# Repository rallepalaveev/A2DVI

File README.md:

# A2DVI - Apple II Digital Video

This is a project for a digital DVI/HDMI Apple II video card.
It directly produces a digital video stream from Apple II's memory content.
The signal is output via an HDMI connector, connecting the Apple II to modern displays with HDMI (or DVI) inputs.
No more analog signal conversion required.

The project is a collaboration with Thorsten Brehm. His related firmware project is here: https://github.com/ThorstenBr/A2DVI-Firmware

For the DVI output to be active, the new firmware developed by Thorsten should be used.

The card also has an alternative analog VGA connector.
For the VGA output to be active, the [VGA firmware](https://github.com/markadev/AppleII-VGA) developed by Mark Aikens should be used.

The card can produce either an analog VGA or a digital HDMI signal, but not both simultaneously.
To switch between modes, a firmware update is required and opening/closing connections.

As of v2.0 VGA function is not supported - the card is DVI only.

V2.2 has an onboard driver to invoke the configuation utility by PR#N, where N is the slot number.

V2.3 is a TH version with 74HC245 and requires a DVI break-out board.

V2.4 is a TH version with 74HC244 and requires a DVI break-out board.

## Procedure to activate DVI mode
* v1.2:
  program [A2DVI-Firmware](https://github.com/ThorstenBr/A2DVI-Firmware) to RPI Pico;
  remove U6 and disconnect pins 11, 12 and 13 of U5.
* v1.5:
  program [A2DVI-Firmware](https://github.com/ThorstenBr/A2DVI-Firmware) to RPI Pico;
  open all 9 DIP switches.
* v1.6:
  program [A2DVI-Firmware](https://github.com/ThorstenBr/A2DVI-Firmware) to RPI Pico;
  desloder the 8 soldering pads at GPIOs 14-21.
* v1.7:
  program [A2DVI-Firmware](https://github.com/ThorstenBr/A2DVI-Firmware) to RPI Pico;
  desloder the 8 soldering pads at GPIOs 14-21; remove VGA sub-board and ribbon cable.
* v2.0:
  program [A2DVI-Firmware](https://github.com/ThorstenBr/A2DVI-Firmware) to RPI Pico.
* v2.2:
  program [A2DVI-Firmware](https://github.com/ThorstenBr/A2DVI-Firmware) to RPI Pico.
* v2.3:
  program [A2DVI-Firmware](https://github.com/ThorstenBr/A2DVI-Firmware) to RPI Pico.
* v2.4:
  program [A2DVI-Firmware](https://github.com/ThorstenBr/A2DVI-Firmware) to RPI Pico.
  
## Procedure to activate VGA mode
* v1.2:
  program [VGA firmware](https://github.com/markadev/AppleII-VGA) to RPI Pico;
  replace U5 and U6.
* v1.5:
  program [VGA firmware](https://github.com/markadev/AppleII-VGA) to RPI Pico;
  close all 9 DIP switches.
* v1.6:
  program [VGA firmware](https://github.com/markadev/AppleII-VGA) to RPI Pico;
  sloder the 8 soldering pads at GPIOs 14-21.
* v1.7:
  program [VGA firmware](https://github.com/markadev/AppleII-VGA) to RPI Pico;
  sloder the 8 soldering pads at GPIOs 14-21; connect VGA sub-board to main board by the ribbon cable.
* v2.0:
  N.A. - v2.0 is HDMI only.
* v2.2:
  N.A. - v2.2 is HDMI only.
* v2.3:
  N.A. - v2.3 is HDMI only.
* v2.4:
  N.A. - v2.4 is HDMI only.
* v4.4:
  N.A. - v4.4 is HDMI only.
* v4.6:
  N.A. - v4.6 is HDMI only.
  * v5.x:
  N.A. - v5.x are HDMI only.

Note: In version 2.4 I experimented with replacing the 8x 270-ohms resistors on the DVI lines by 100pF capacitors to achieve better separation form potential 3.3V DC leak from the screen; while this worked, some screens are more prone to noise and results may still be better with the 270-ohms resistors.

Note2: Version 4.4 is bidirectional and can work as a variety of functionalities. Firmware is closed source so far. V4.6 has some optimizations.

Note3: Versions 5.x are based on CPB with RP2354B and are 5V tolerant and has 48 GPIOs available. This eliminates the need
for level shifting and multiplexing. This version had DVI function and can support RTC via a dedicated connector.

## Dual-Language Support
The pin on the v1.5 and later boards is for AltChr connection, supported by A2DVI firmware for switching between alternative character sets on non-US versions of Apple II ("Euro-machines").

# Hardware
* Based on the PICO controller board.
* Provides a DVI video stream via an HDMI connector.
* Low power/heat dissipation: less than 70mA@5V = 0.35W in operation.
* Uses 4x 74LV245 bus transceivers for 5V/3.3V signal conversion of the Apple II bus.
* Separate ALTCHR input pin for dual-language support: pin needs to be wired separately to the "language switch" of Euro-Apple IIs (optional).
* Versions 5.x do not need level shifters.

# Thanks
This is a project based on:

* the AppleII-VGA project by Mark Aikens - https://github.com/markadev/AppleII-VGA

* the PicoDVI project by Luke Wren - https://github.com/Wren6991/PicoDVI

* Thorsten Brehm for firmware development and board design considerations

* Oliver Schmidt on original idea discussions and design considerations

* Mike Neil for adapting the firmware for v5.x.

# License
Board design by Ralle Palaveev (c) 2026.

All rights reserved.

Redistribution and use in source, binary, and manufactured forms, with or without
modification, are permitted provided that the following conditions are met:
1. Redistributions of source code and design files must retain the above copyright
   notice, this list of conditions and the following disclaimer.
2. Redistributions in binary or manufactured form must reproduce the above copyright
   notice, this list of conditions and the following disclaimer in the
   documentation and/or other materials provided with the distribution.
3. All advertising materials mentioning features or use of this software
   or hardware must display the following acknowledgement:
   This product includes software or hardware developed by Ralle Palaveev.
4. Neither the name of Ralle Palaveev nor the
   names of its contributors may be used to endorse or promote products
   derived from this software or hardware without specific prior written permission.

The above copyright notice and this permission notice shall be included in all
copies or substantial portions of the Software.

THE SOFTWARE IS PROVIDED "AS IS", WITHOUT WARRANTY OF ANY KIND, EXPRESS OR
IMPLIED, INCLUDING BUT NOT LIMITED TO THE WARRANTIES OF MERCHANTABILITY,
FITNESS FOR A PARTICULAR PURPOSE AND NONINFRINGEMENT. IN NO EVENT SHALL THE
AUTHORS OR COPYRIGHT HOLDERS BE LIABLE FOR ANY CLAIM, DAMAGES OR OTHER
LIABILITY, WHETHER IN AN ACTION OF CONTRACT, TORT OR OTHERWISE, ARISING FROM,
OUT OF OR IN CONNECTION WITH THE SOFTWARE OR THE USE OR OTHER DEALINGS IN THE
SOFTWARE.

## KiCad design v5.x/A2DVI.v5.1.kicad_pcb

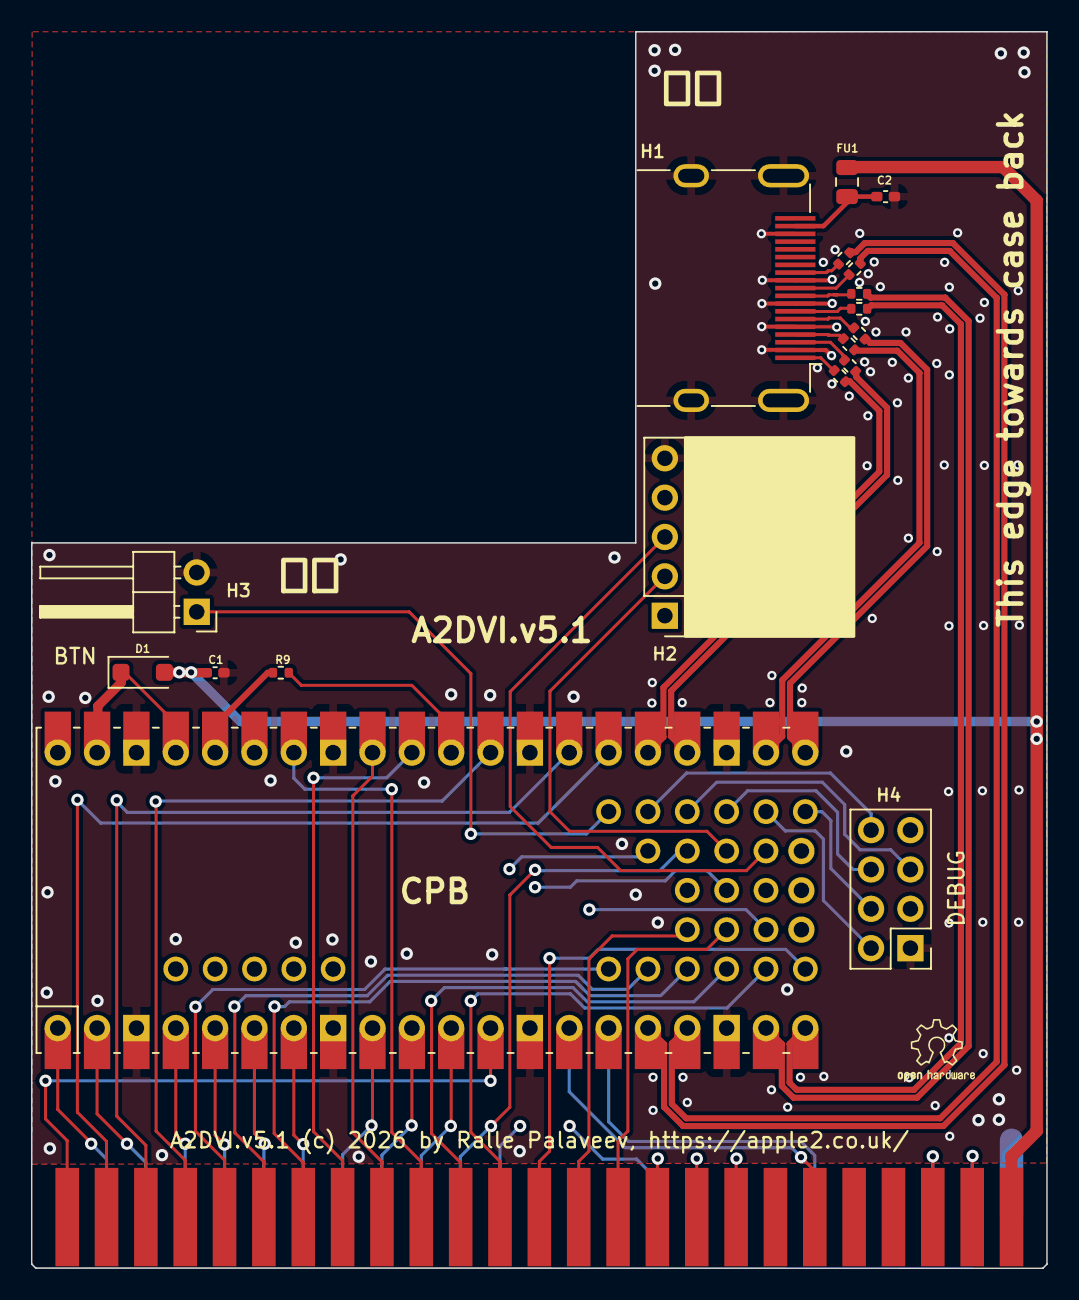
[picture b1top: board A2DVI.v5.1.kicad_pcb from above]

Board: 4 copper layers, 65.5 x 79.8 mm, 18 parts (0 on the bottom side), 22 nets.

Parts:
C1, C2: 100n; C_0402_1005Metric_Pad0.74x0.62mm_HandSolder
D1: D_SOD-123F
FU1: 100mA; Fuse_0805_2012Metric
H1: HDMI_A_Molex_208658-1001_Horizontal
H2: PinHeader_1x05_P2.54mm_Vertical
H3: PinHeader_1x02_P2.54mm_Horizontal
H4: PinHeader_2x04_P2.54mm_Vertical
R1, R2, R3, R4, R5, R6, R7, R8: 270; R_0402_1005Metric
R9: 1k; R_0402_1005Metric
U1: CPB; CPB_SMD_TH

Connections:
3.3V: H2.1, H4.7, R9.2, U1.36
5V: C1.2, D1.2, FU1.2
5V_out: C2.2, FU1.1, H1.18
BTN: H3.1, U1.41
CLK_N: R8.1, U1.16
CLK_P: R7.1, U1.17
CS: H4.4, U1.46
D0_N: R6.1, U1.19
D0_P: R5.1, U1.20
D1_N: R4.1, U1.21
D1_P: R3.1, U1.22
D2_N: R2.1, U1.24
D2_P: R1.1, U1.25
GND: C1.1, C2.1, H1.2, H1.5, H1.8, H1.11, H1.17, H1.SH, H2.5, H3.2, H4.1, U1.3, U1.8, U1.13, U1.18, U1.23, U1.28, U1.33, U1.38
I2C_SCL: H2.3, U1.50
I2C_SDA: H2.2, U1.49
LED: H4.8, U1.42
RUN: R9.1, U1.30
UART_RX: H4.6, U1.44
UART_TX: H4.5, U1.43
UART_extra: H4.2, U1.45
VSYS: D1.1, U1.37, U1.39

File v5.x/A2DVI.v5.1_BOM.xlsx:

Comment | Designator | Footprint | JLCPCB Part #（optional）
16V 100nF X7R ±10% 0402 Multilayer Ceramic Capacitors MLCC - SMD/SMT ROHS | C1,C2 | 0402 | C1525
DSS14 | D1 | SOD-123FL | C2923923
6V 500mA Resettable Fuse | FU1 | 0805-50 | C269104
HDMI connector | H1 |  | C2906135
270 | R1,R2,R3,R4,R5,R6,R7,R8 | 0402 | C324790
1k | R9 | 0402 | C11702

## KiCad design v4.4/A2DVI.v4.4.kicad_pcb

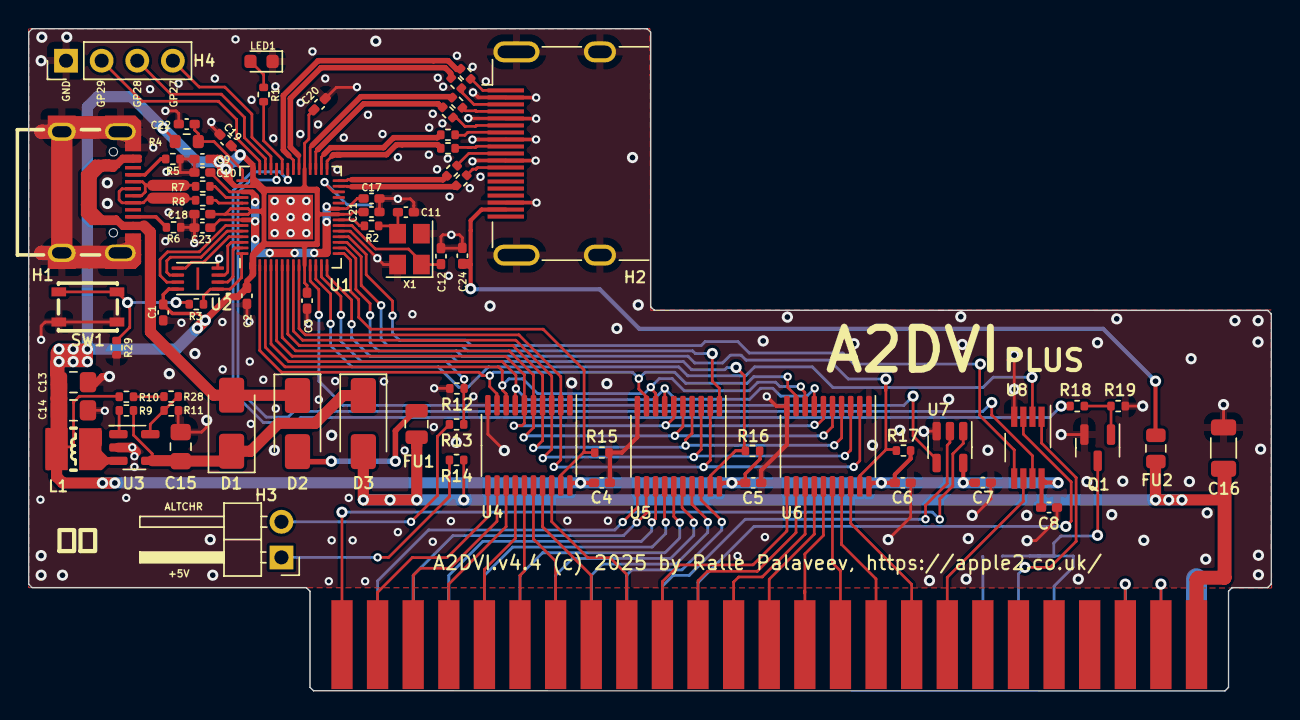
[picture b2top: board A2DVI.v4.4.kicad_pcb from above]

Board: 2 copper layers, 88.6 x 47.2 mm, 75 parts (0 on the bottom side), 63 nets.

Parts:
C1, C2, C3, C4, C5, C6, C7, C8, C17, C18, C19, C20, C21, C22, C23, C24: 100n; C_0402_1005Metric_Pad0.74x0.62mm_HandSolder
C9, C10: 2u2; C_0402_1005Metric_Pad0.74x0.62mm_HandSolder
C11, C12: 15p; C_0402_1005Metric_Pad0.74x0.62mm_HandSolder
C13, C14, C15: 22uF; C_0805_2012Metric_Pad1.18x1.45mm_HandSolder
C16: 100uF; C_1206_3216Metric
D1, D2, D3: SS14; D_SMA
FU1: 500mA; Fuse_0805_2012Metric
FU2: 100mA; Fuse_0805_2012Metric
H1: USB-C-16P-F(A40-00119-A52-12); USB2.0_TYPE-C(A40-00119-A52-12)
H2: HDMI_A_Molex_208658-1001_Horizontal
H3: PinHeader_1x02_P2.54mm_Horizontal
H4: PinHeader_1x04_P2.54mm_Vertical
L1: 2.2uH/1.5A/DCR=58mR/20%/3.00x3.00x1.50mm/CD32(NRS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; CD32
LED1: LED_0603_1608Metric
Q1: 2N7002; SOT-23
R1, R2, R3, R14, R18: 1k; R_0402_1005Metric
R4: 200; R_0603_1608Metric
R5, R6: 5k1; R_0402_1005Metric
R7, R8: 27; R_0402_1005Metric
R9: 1M; R_0402_1005Metric
R10: 220k 1%; R_0402_1005Metric
R11: 49.9k 1%; R_0402_1005Metric
R12, R15, R16, R17, R19: 10k; R_0402_1005Metric
R13: 5k; R_0402_1005Metric
R20, R21, R22, R23, R24, R25, R26, R27: 270; R_0402_1005Metric
R28: 5.1k 1%; R_0402_1005Metric
R29: 100k; R_0402_1005Metric
SW1: YTS-A016-X
U1: QFN-56-1EP_7x7mm_P0.4mm_EP3.2x3.2mm
U2: W25Q16JVUXIQ; Winbond_USON-8-1EP_3x2mm_P0.5mm_EP0.2x1.6mm
U3: SY8089AAAC, SOT-23-5; SOT-23-5
U4, U5, U6: SN74LVC245APWR; TSSOP-20_4.4x6.5mm_P0.65mm
U7: 74LVC1G08, SOT-23-5; SOT-23-5
U8: 74LVC3G34, VSSOP-8_3.0x3.0mm_P0.65mm; VSSOP-8_3.0x3.0mm_P0.65mm
X1: ABM8-272-T3 12MHz; Crystal_SMD_3225-4Pin_3.2x2.5mm

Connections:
1.1V: C10.2, C17.1, C23.2, U1.23, U1.45, U1.50
3.3V: C1.2, C2.2, C3.2, C4.1, C5.1, C6.1, C7.1, C8.1, C9.2, C13.1, C14.1, C18.2, C19.2, C20.1, C21.1, L1.2, R4.1, R10.2, R16.2, R17.2, U1.1, U1.10, U1.22, U1.33, U1.42, U1.44, U1.48, U1.49, U2.8, U4.20, U5.20, U6.20, U7.5, U8.8
3.3V-en: R9.2, U3.1
3.3V-out: L1.1, U3.3
5V: C16.1, D3.2, FU1.2, FU2.2, R14.2
5V-1: D2.2, FU1.1
5V-2: H3.1, R14.1
5V_out: C24.2, FU2.1, H2.18
AD0: U1.2, U4.9, U5.9, U6.9
AD1: U1.3, U4.8, U5.8, U6.8
AD2: U1.4, U4.7, U5.7, U6.7
AD3: U1.5, U4.6, U5.6, U6.6
AD4: U1.6, U4.5, U5.5, U6.5
AD5: U1.7, U4.4, U5.4, U6.4
AD6: U1.8, U4.3, U5.3, U6.3
AD7: U1.9, U4.2, U5.2, U6.2
ADCVDD: C22.2, R4.2, U1.43
Altchr: H3.2, R13.1
C-A5: H1.A5, R5.1
C-B5: H1.B5, R6.1
CK_N: R27.1, R27.2, U1.27
CK_P: H2.10, R26.1, R26.2, U1.28
D0_N: H2.9, R25.1, R25.2, U1.29
D0_P: H2.7, R24.1, R24.2, U1.30
D1_N: H2.6, R23.1, R23.2, U1.31
D1_P: H2.4, R22.1, R22.2, U1.32
D2_N: H2.3, R21.1, R21.2, U1.34
D2_P: H2.1, R20.1, R20.2, U1.35
DATADIR: U1.17, U5.1
DATAOE: R16.1, U1.14, U5.19
FB: R11.2, R28.2, U3.5
FB1: R10.1, R28.1
GND: C1.1, C2.1, C3.1, C4.2, C5.2, C6.2, C7.2, C8.2, C9.1, C10.1, C11.2, C12.1, C13.2, C14.2, C15.1, C16.2, C17.2, C18.1, C19.1, C20.2, C21.2, C22.1, C23.1, C24.1, H1.0, H1.A1, H1.A12, H1.B1, H1.B12, H2.2, H2.5, H2.8, H2.11, H2.17, H2.SH, H4.1, LED1.1, Q1.2, R5.2, R6.2, R11.1, R12.1, R15.2, R19.2, R29.1, SW1.2, U1.19, U1.57, U2.4, U3.2, U4.1, U4.10, U5.10, U6.1, U6.10, U7.3, U8.4, X1.2, X1.4
GP25: R1.2, U1.37
GP27: H4.4, U1.39
GP28: H4.3, U1.40
GP29: H4.2, U1.41
IRQ-i: Q1.1, R18.2, R19.1
L-Altchr: R12.2, R13.2, U1.13
L-IRQ: R18.1, U1.36
L-PHI0: U1.18, U8.5
L-RW: U1.12, U8.2
L-Reset: U1.38, U8.7
LED: LED1.2, R1.1
LSBOE: R15.1, U1.15, U4.19
MSBOE: R17.1, U1.16, U6.19
QSPI_SCLK: U1.52, U2.6
QSPI_SD0: U1.53, U2.5
QSPI_SD1: U1.55, U2.2
QSPI_SD2: U1.54, U2.3
QSPI_SD3: U1.51, U2.7
QSPI_SS: R3.2, U1.56, U2.1
SW: R3.1, R29.2, SW1.1
Select: U1.11, U7.4
USB_DM: H1.A7, H1.B7, R7.1
USB_DMX: R7.2, U1.46
USB_DP: H1.A6, H1.B6, R8.1
USB_DPX: R8.2, U1.47
VBUS: D1.2, D2.1, H1.A4, H1.A9, H1.B4, H1.B9
VSYS: C15.2, D1.1, D3.1, R9.1, U3.4
XIN: C12.2, U1.20, X1.1
XOUT: R2.1, U1.21
XOUT1: C11.1, R2.2, X1.3

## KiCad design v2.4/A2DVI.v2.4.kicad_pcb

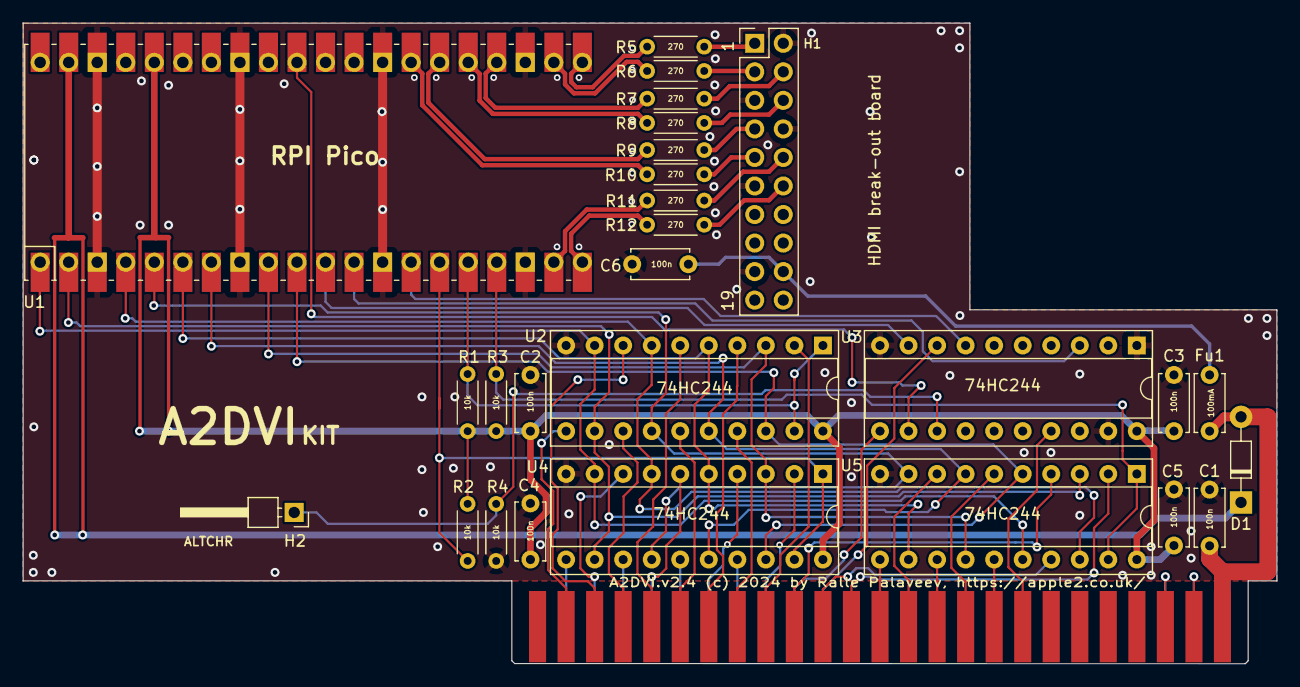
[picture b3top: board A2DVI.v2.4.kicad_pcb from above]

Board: 2 copper layers, 111.6 x 57.0 mm, 27 parts (0 on the bottom side), 29 nets.

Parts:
C1, C2, C3, C4, C5, C6: 100n; C_Disc_D5.0mm_W2.5mm_P5.00mm
D1: D_DO-34_SOD68_P7.62mm_Horizontal
Fu1: 100mA; C_Disc_D5.0mm_W2.5mm_P5.00mm
H1: PinHeader_2x10_P2.54mm_Vertical
H2: PinHeader_1x01_P2.54mm_Horizontal
R1, R2, R3, R4: 10k; R_Axial_DIN0204_L3.6mm_D1.6mm_P5.08mm_Horizontal
R5, R6, R7, R8, R9, R10, R11, R12: 270; R_Axial_DIN0204_L3.6mm_D1.6mm_P5.08mm_Horizontal
U1: Pico; RPi_PicoW_SMD_TH
U2, U3, U4, U5: 74HC244; DIP-20_W7.62mm_Socket

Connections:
3.3V: C2.1, C3.1, C4.1, C5.1, R1.2, R2.2, R3.2, U1.36 (3V3), U2.20, U3.20, U4.20, U5.20
5V: C1.2, D1.2, Fu1.1
5Vout: C6.2, Fu1.2, H1.18
AD0: U1.1 (GPIO0), U2.9, U4.9, U5.16
AD1: U1.2 (GPIO1), U2.12, U4.12, U5.3
AD2: U1.4 (GPIO2), U2.7, U4.7, U5.18
AD3: U1.5 (GPIO3), U2.14, U4.14, U5.9
AD4: U1.6 (GPIO4), U2.5, U4.5, U5.12
AD5: U1.7 (GPIO5), U2.16, U4.16, U5.7
AD6: U1.9 (GPIO6), U2.3, U4.3, U5.14
AD7: U1.10 (GPIO7), U2.18, U4.18, U5.5
AltChr: H2.1, R4.2, U3.13
CK_N: H1.12, R12.1, R12.2, U1.20 (GPIO15)
CK_P: H1.10, R11.1, R11.2, U1.19 (GPIO14)
D0_N: H1.9, R10.1, R10.2, U1.27 (GPIO21)
D0_P: H1.7, R9.1, R9.2, U1.26 (GPIO20)
D1_N: H1.6, R8.1, R8.2, U1.25 (GPIO19)
D1_P: H1.4, R7.1, R7.2, U1.24 (GPIO18)
D2_N: H1.3, R6.1, R6.2, U1.22 (GPIO17)
D2_P: H1.1, R5.1, R5.2, U1.21 (GPIO16)
DATAOE: R2.1, U1.15 (GPIO11), U4.1, U4.19
GND: C1.1, C2.2, C3.2, C4.2, C5.2, C6.1, H1.2, H1.5, H1.8, H1.11, H1.17, R4.1, U1.3 (GND), U1.8 (GND), U1.13 (GND), U1.18 (GND), U1.23 (GND), U1.28 (GND), U1.33 (AGND), U1.38 (GND), U2.10, U3.1, U3.10, U3.19, U4.10, U5.10
L-AltChr: U1.14 (GPIO10), U3.7
L-DevSel: U1.11 (GPIO8), U3.9
L-PHI0: U1.31 (GPIO26_ADC0), U3.12
L-RW: U1.12 (GPIO9), U3.3
LSBOE: R1.1, U1.16 (GPIO12), U2.1, U2.19
MSBOE: R3.1, U1.17 (GPIO13), U5.1, U5.19
VSYS: D1.1, U1.39 (VSYS)

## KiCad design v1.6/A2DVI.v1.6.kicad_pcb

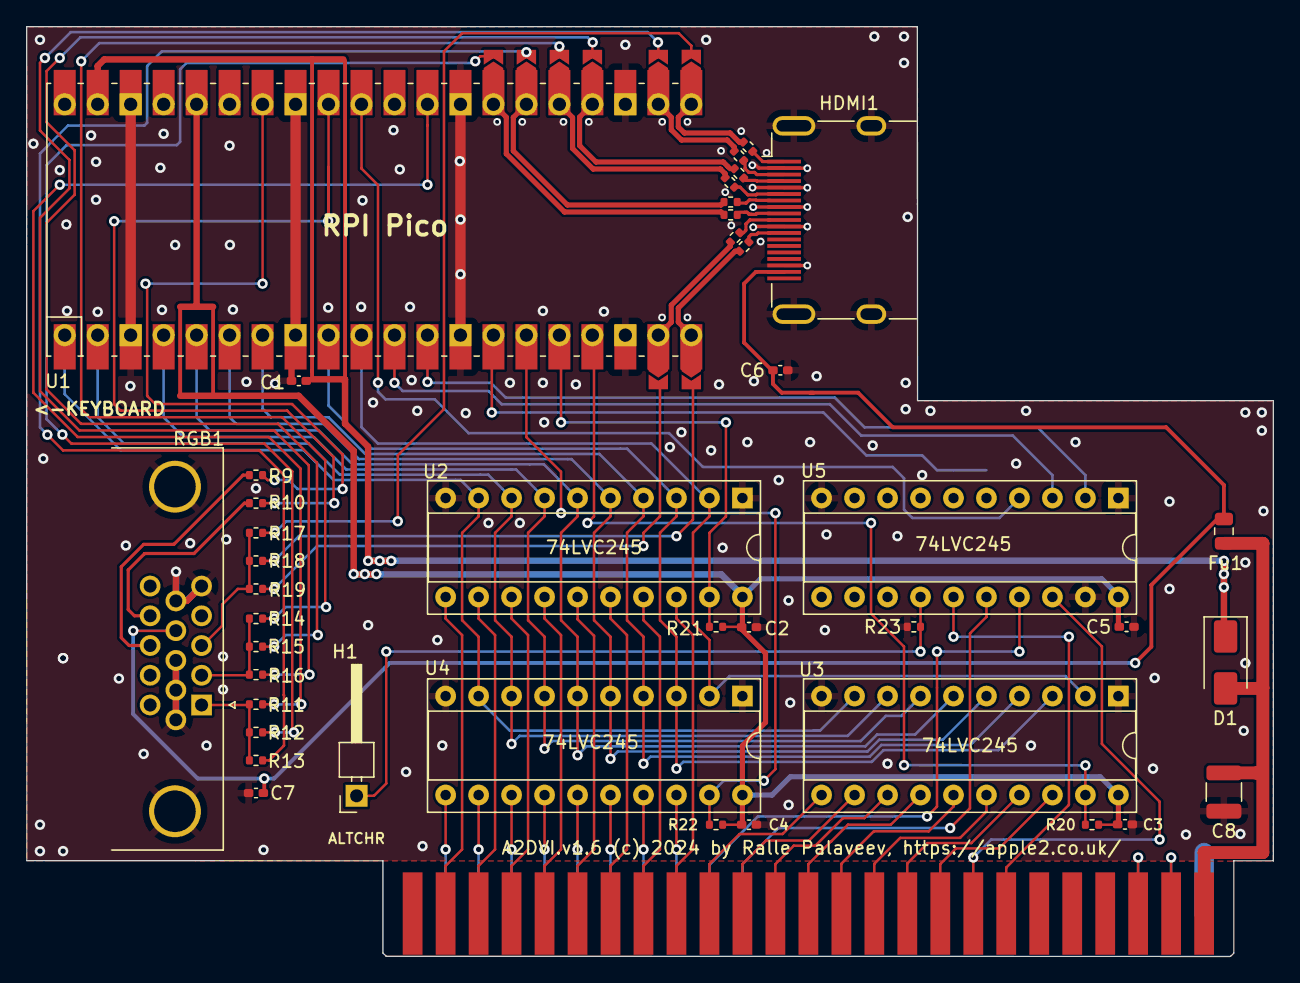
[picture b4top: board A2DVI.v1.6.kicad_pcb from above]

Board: 2 copper layers, 96.0 x 71.6 mm, 41 parts (0 on the bottom side), 37 nets.

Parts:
C1, C2, C3, C4, C5, C6, C7: 100n; C_0402_1005Metric_Pad0.74x0.62mm_HandSolder
C8: C_1210_3225Metric
D1: SS16; D_SMA
Fu1: Fuse_0805_2012Metric
H1: PinHeader_1x01_P2.54mm_Horizontal
HDMI1: HDMI_A_Molex_208658-1001_Horizontal
R1, R2, R3, R4, R5, R6, R7, R8: 270; R_0402_1005Metric
R9, R10: 47; R_0402_1005Metric
R11, R14, R17: 510; R_0402_1005Metric
R12, R15, R18: 1k; R_0402_1005Metric
R13, R16, R19: 2k; R_0402_1005Metric
R20, R21, R22: 10k; R_0402_1005Metric
R23: 5k; R_0402_1005Metric
RGB1: DB15_Female_HighDensity_MountingHoles; DSUB-15-HD_Female_Horizontal_P2.29x1.98mm_EdgePinOffset3.03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
U1: Pico; RPi_PicoW_SMD_TH
U2, U3, U4, U5: 74LVC245; DIP-20_W7.62mm_Socket

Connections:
3.3V: C2.1, C3.2, C4.1, C5.2, R20.2, R21.2, R22.2, U1.36 (3V3), U2.20, U3.20, U4.20, U5.20
5V: C8.2, D1.2, Fu1.2
5V_out: C6.2, C7.1, Fu1.1, HDMI1.18, RGB1.9
AD0: U1.1 (GPIO0), U2.9, U3.9, U4.9
AD1: U1.2 (GPIO1), U2.8, U3.8, U4.8
AD2: U1.4 (GPIO2), U2.7, U3.7, U4.7
AD3: U1.5 (GPIO3), U2.6, U3.6, U4.6
AD4: U1.6 (GPIO4), U2.5, U3.5, U4.5
AD5: U1.7 (GPIO5), U2.4, U3.4, U4.4
AD6: U1.9 (GPIO6), U2.3, U3.3, U4.3
AD7: U1.10 (GPIO7), U2.2, U3.2, U4.2
Altchr: H1.1, R23.2, U5.14
B_out: R17.1, R18.1, R19.1, RGB1.3
CK_N: R8.1, U1.20 (GPIO15)
CK_P: R7.1, U1.19 (GPIO14)
D0_N: R6.1, U1.27 (GPIO21)
D0_P: R5.1, U1.26 (GPIO20)
D1_N: R4.1, U1.25 (GPIO19)
D1_P: R3.1, U1.24 (GPIO18)
D2_N: R2.1, U1.22 (GPIO17)
D2_P: R1.1, U1.21 (GPIO16)
D2_otut_P: HDMI1.1, R1.2
DATAOE: R22.1, U1.15 (GPIO11), U4.19
GND: C1.1, C2.2, C3.1, C4.2, C5.1, C6.1, C7.2, C8.1, HDMI1.2, HDMI1.5, HDMI1.8, HDMI1.11, HDMI1.17, HDMI1.SH, R23.1, RGB1.0, RGB1.5, RGB1.6, RGB1.7, RGB1.8, RGB1.10, U1.3 (GND), U1.8 (GND), U1.13 (GND), U1.18 (GND), U1.23 (GND), U1.28 (GND), U1.33 (AGND), U1.38 (GND), U2.1, U2.10, U3.1, U3.10, U4.1, U4.10, U5.1, U5.10, U5.19
G_out: R14.1, R15.1, R16.1, RGB1.2
HSYNC: R9.2, U1.34 (GPIO28_ADC2)
HSYNC_out: R9.1, RGB1.13
L-DevSel: U1.11 (GPIO8), U5.3
L-PHI0: U1.31 (GPIO26_ADC0), U5.4
L-RW: U1.12 (GPIO9), U5.2
LSBOE: R21.1, U1.16 (GPIO12), U2.19
MSBOE: R20.1, U1.17 (GPIO13), U3.19
R0: R11.2, U1.29 (GPIO22)
R_out: R11.1, R12.1, R13.1, RGB1.1
VSYNC: R10.2, U1.32 (GPIO27_ADC1)
VSYNC_out: R10.1, RGB1.14
VSYS: C1.2, D1.1, U1.39 (VSYS)

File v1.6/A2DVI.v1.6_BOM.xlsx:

Comment | Designator | Footprint | JLCPCB Part #（optional）
HDMI connector | HDMI1 |  | C7501808
270 | R1,R2,R3,R4,R5,R6,R7,R8 | 0402 | C25099
49.9 | R9,R10 | 0402 | C25120
510 | R11,R14,R17 | 0402 | C25123
1k | R12,R15,R18 | 0402 | C11702
2k | R13,R16,R19 | 0402 | C4109
4.3k | R23 | 0402 | C407732
10k | R20,R21,R22 | 0402 | C25744
16V 100nF X7R ±10% 0402 Multilayer Ceramic Capacitors MLCC - SMD/SMT ROHS | C1,C2,C3,C4,C5,C6,C7 | 0402 | C1525
10V 100uF X5R ±20% 1210 Multilayer Ceramic Capacitors MLCC - SMD/SMT ROHS | C8 | 1210 | C386065
SS16 SBD | D1 | SMA(DO-214AC) | C908233
6V 100mA Resettable Fuse | Fu1 | 0805 | C20975

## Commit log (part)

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2024-03-09 Rename A2DVI.v1.2.png to A2DVI.v1.2.render.png
2024-07-07 Rename A2DVI.jpg to v1.2/A2DVI.jpg
2024-07-07 Rename A2DVI.v1.2.render.png to v1.2/A2DVI.v1.2.render.png
2024-07-07 Rename A2DVI.v1.2.sch.pdf to v1.2/A2DVI.v1.2.sch.pdf
2024-07-07 Rename A2DVI.v1.6.sch.pdf to v1.6/A2DVI.v1.6.sch.pdf
2024-07-07 Rename A2DVI.jpg to A2DVI.v1.2.jpg
2024-07-07 Rename A2DVI.v1.5.sch.pdf to v1.5/A2DVI.v1.5.sch.pdf
2024-07-08 Added firmware project link.
2024-07-08 Updated project description.
2024-07-13 Rename A2DVI.v1.3.jpg to v1.3/A2DVI.v1.3.jpg
2024-07-23 Rename A2DVI.v1.7.sch.pdf to A2DVI.v1.7.sch.pdf
2024-07-23 Rename A2DVI.v2.0.sch.pdf to A2DVI.v2.0.sch.pdf
2025-04-24 Create file
2025-10-07 new.txt
2025-11-17 Update Manual.md with A2DVI v4.4 details
    Added detailed project description and firmware functionalities for A2DVI v4.4.
2025-11-17 Update Z80 emulator description with image link
2025-11-17 Update link for Z80 emulator example disk
2025-11-17 Fix header formatting in Manual.md
2025-11-24 Revise Apple II Mouse Card details and FDD note
    Updated the Apple II Mouse Card descriptions and restructured the numbering for clarity. Added a note about the FDD functionality working on IIe only.
2025-11-24 Consolidate floppy disk image instructions in Manual.md
2026-03-16 Rename manual.md to Manual.md
2026-03-16 Update Manual.md with A2DVI v4.6 details
    Added detailed documentation for A2DVI v4.6, including project overview, firmware functions, and usage instructions.
2026-04-15 Add version 4.6 information to README

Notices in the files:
v1.6/A2DVI.v1.6.kicad_pcb:
A2DVI.v1.6 (c) 2024 by Ralle Palaveev, https://apple2.co.uk
A2DVI.v1.6 board design by R. Palaveev, (c) 2024
VGA firmware by Mark Aikens, (c) 2021-2022
DVI Firmware by Thorsten Brehm, (c) 2024
v2.4/A2DVI.v2.4.kicad_pcb:
A2DVI.v2.4 (c) 2024 by Ralle Palaveev, https://apple2.co.uk
Board design by R. Palaveev, (c) 2025
Firmware by Thorsten Brehm, (c) 2025
v4.4/A2DVI.v4.4.kicad_pcb:
Board design by Ralle Palaveev, (c) 2025
A2DVI.v4.4 (c) 2025 by Ralle Palaveev, https://apple2.co.uk
v5.x/A2DVI.v5.1.kicad_pcb:
Firmware by Mike Neil, (c) 2026
Based on work by: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
